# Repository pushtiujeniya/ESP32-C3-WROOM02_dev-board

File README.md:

# ESP32-C3-WROOM-02 Development Board

## Overview

This project is a custom 2-layer development board designed around the ESP32-C3-WROOM-02 Wi‑Fi + Bluetooth MCU module. The board includes USB Type‑C power input, onboard 3.3V regulation, boot/reset circuitry, GPIO breakout headers, and USB protection components.

## Features

* ESP32-C3-WROOM-02 module
* USB Type‑C interface
* Onboard 3.3V regulator
* Boot and reset buttons
* GPIO breakout headers
* USB ESD protection
* Power indicator LED
* 2-layer PCB design

## Applications

* IoT devices
* Embedded development
* Sensor interfacing
* Wireless communication projects
* Learning and prototyping

## Hardware Included

* ESP32-C3-WROOM-02 MCU module
* USB Type‑C connector
* Voltage regulator
* Decoupling capacitors
* ESD protection devices
* Boot/reset circuitry
* GPIO expansion headers

## Notes

* Operates on 3.3V logic
* Powered through USB Type‑C
* Suitable for firmware development using ESP-IDF or Arduino framework

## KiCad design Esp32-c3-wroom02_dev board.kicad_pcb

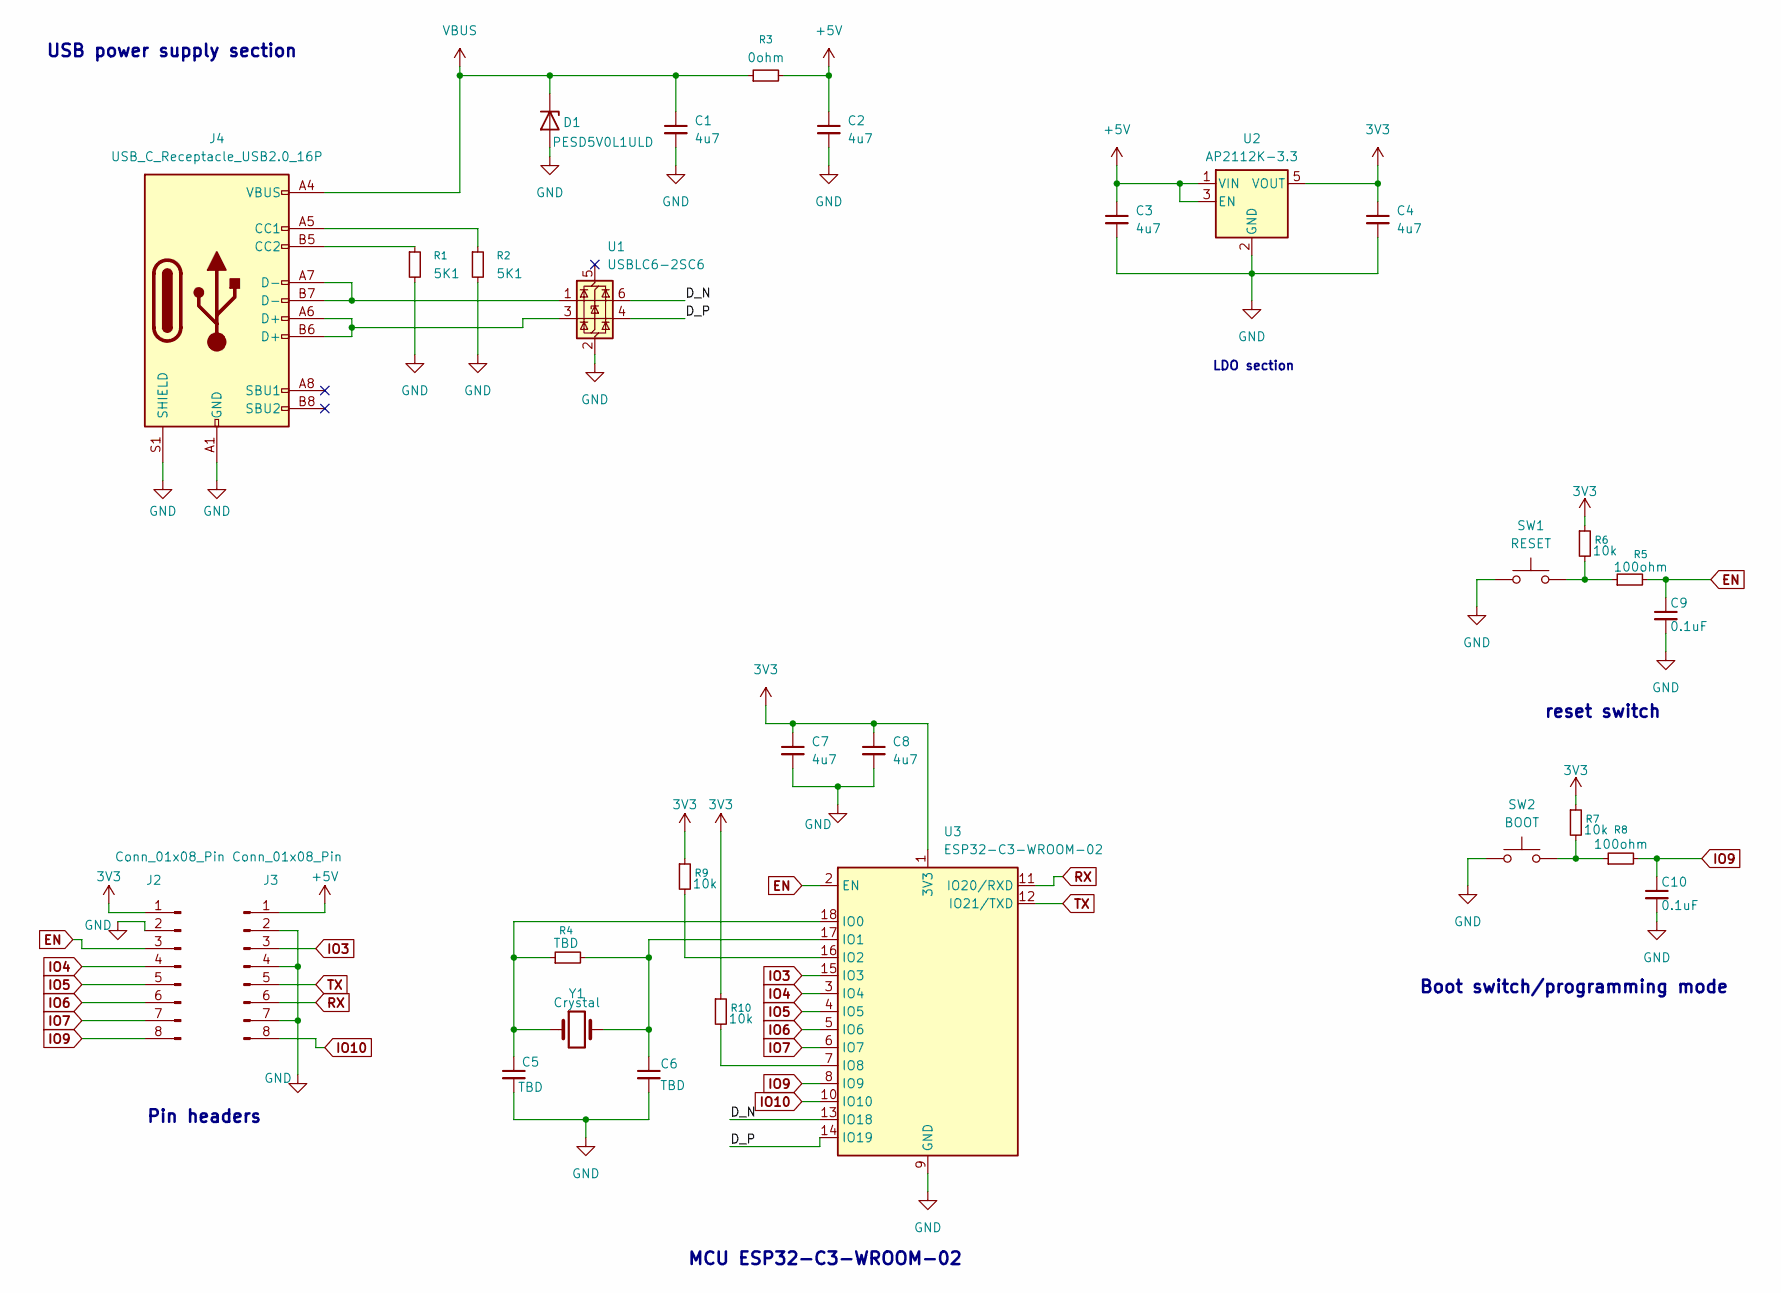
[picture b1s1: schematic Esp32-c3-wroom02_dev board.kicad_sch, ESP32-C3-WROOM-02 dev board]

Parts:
C1, C2, C3, C4, C7, C8: 4u7; C_0805_2012Metric
C5, C6: TBD; C_0402_1005Metric
C9, C10: 0.1uF; C_0402_1005Metric
D1: PESD5V0L1ULD; D_SOD-882D
J2, J3: Conn_01x08_Pin; PinHeader_1x08_P2.54mm_Vertical
J4: USB_C_Receptacle_USB2.0_16P; USB_C_Receptacle_G-Switch_GT-USB-7010ASV
R1, R2: 5K1; R_0402_1005Metric
R3: 0ohm; R_0805_2012Metric
R4: TBD; R_0201_0603Metric
R5, R8: 100ohm; R_0402_1005Metric
R6, R7, R9, R10: 10k; R_0402_1005Metric
SW1: RESET; SW_SPST_B3U-1000P
SW2: BOOT; SW_SPST_B3U-1000P
U1: USBLC6-2SC6; SOT-23-6
U2: AP2112K-3.3; SOT-23-5
U3: ESP32-C3-WROOM-02
Y1: Crystal; Crystal_SMD_3215-2Pin_3.2x1.5mm

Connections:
3V3: C4.1, C7.1, C8.1, J2.1, R6.1, R7.1, R9.1, R10.1, U2.5 (VOUT), U3.1 (3V3)
+5V: C2.1, C3.1, J3.1, R3.2, U2.1 (VIN), U2.3 (EN)
/D_N: U1.6 (I/O1), U3.13 (IO18)
/D_P: U1.4 (I/O2), U3.14 (IO19)
EN: C9.1, J2.3, R5.2, U3.2 (EN)
GND: C1.2, C2.2, C3.2, C4.2, C5.2, C6.2, C7.2, C8.2, C9.2, C10.2, D1.2 (A), J2.2, J3.2, J3.4, J3.7, J4.A1 (GND), J4.A12 (GND), J4.B1 (GND), J4.B12 (GND), J4.S1 (SHIELD), R1.2, R2.2, SW1.1, SW2.1, U1.2 (GND), U2.2 (GND), U3.9 (GND), U3.19 (GND)
IO3: J3.3, U3.15 (IO3)
IO4: J2.4, U3.3 (IO4)
IO5: J2.5, U3.4 (IO5)
IO6: J2.6, U3.5 (IO6)
IO7: J2.7, U3.6 (IO7)
IO9: C10.1, J2.8, R8.2, U3.8 (IO9)
IO10: J3.8, U3.10 (IO10)
unnamed: J4.A5 (CC1), R2.1
unnamed: J4.B5 (CC2), R1.1
unnamed: J4.A6 (D+), J4.B6 (D+), U1.3 (I/O2)
unnamed: J4.A7 (D-), J4.B7 (D-), U1.1 (I/O1)
unnamed: R5.1, R6.2, SW1.2
unnamed: R7.2, R8.1, SW2.2
unnamed: C5.1, R4.1, U3.18 (IO0), Y1.1
unnamed: C6.1, R4.2, U3.17 (IO1), Y1.2
unnamed: R9.2, U3.16 (IO2)
unnamed: R10.2, U3.7 (IO8)
RX: J3.6, U3.11 (IO20/RXD)
TX: J3.5, U3.12 (IO21/TXD)
VBUS: C1.1, D1.1 (K), J4.A4 (VBUS), J4.A9 (VBUS), J4.B4 (VBUS), J4.B9 (VBUS), R3.1

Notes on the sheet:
Pin headers
Boot switch/programming mode
reset switch
LDO section
USB power supply section
MCU ESP32-C3-WROOM-02

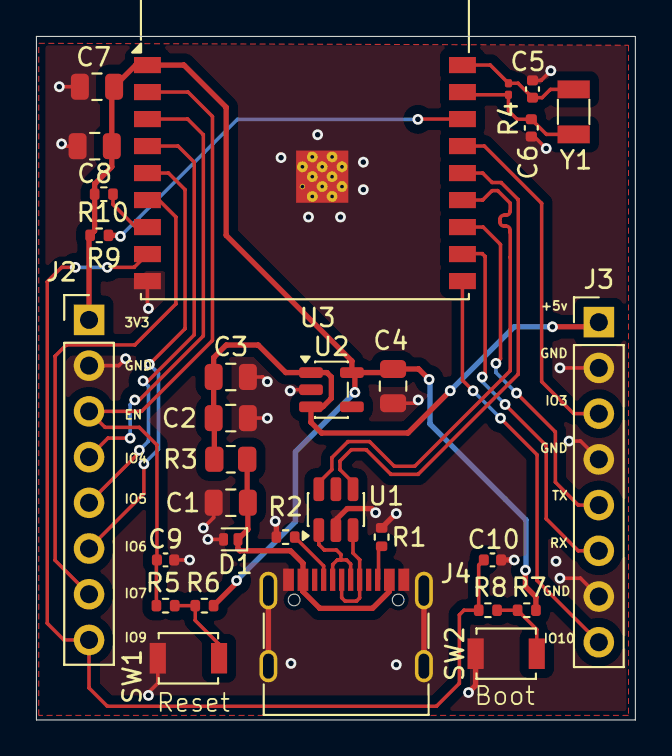
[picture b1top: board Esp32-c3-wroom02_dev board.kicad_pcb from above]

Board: 2 copper layers, 33.3 x 38.0 mm, 30 parts (0 on the bottom side), 26 nets.

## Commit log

2026-05-04 Add new temporary file
2026-05-04 technical document pdf added
2026-05-18 schematic file added
2026-05-18 Create temp file
2026-05-18 3D images added
2026-05-18 schematic pdf added
2026-05-18 layout pdf file added
2026-05-18 project file added
2026-05-18 layout file added
2026-05-18 Create temp
2026-05-18 back up files added
2026-05-18 Add README for ESP32-C3-WROOM-02 development board
    This README provides an overview of the ESP32-C3-WROOM-02 development board, detailing its features, applications, included hardware, and operational notes.
